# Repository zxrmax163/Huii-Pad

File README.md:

# Huii-Pad 

Is a small Macropad wich has 10 keys and a oled screen.

the cas is desinged to be printed in FDM with a pressfit cover and a SLA printed window for the controller. The case holds together by friction and the pcb gets screwt in with M3 Bolts and is hold by M3 Nuts in the case.

# PCB

The PCB is 100mm width and has a lenght of 68mm.

# Firmware

KMK with support for OLED screen.

# BOM

10x Cherry MX Switches

10x DSA Keycaps

1x 0.91" 128x32 OLED Display

1x XIAO RP2040

1x Case (3d printed parts)

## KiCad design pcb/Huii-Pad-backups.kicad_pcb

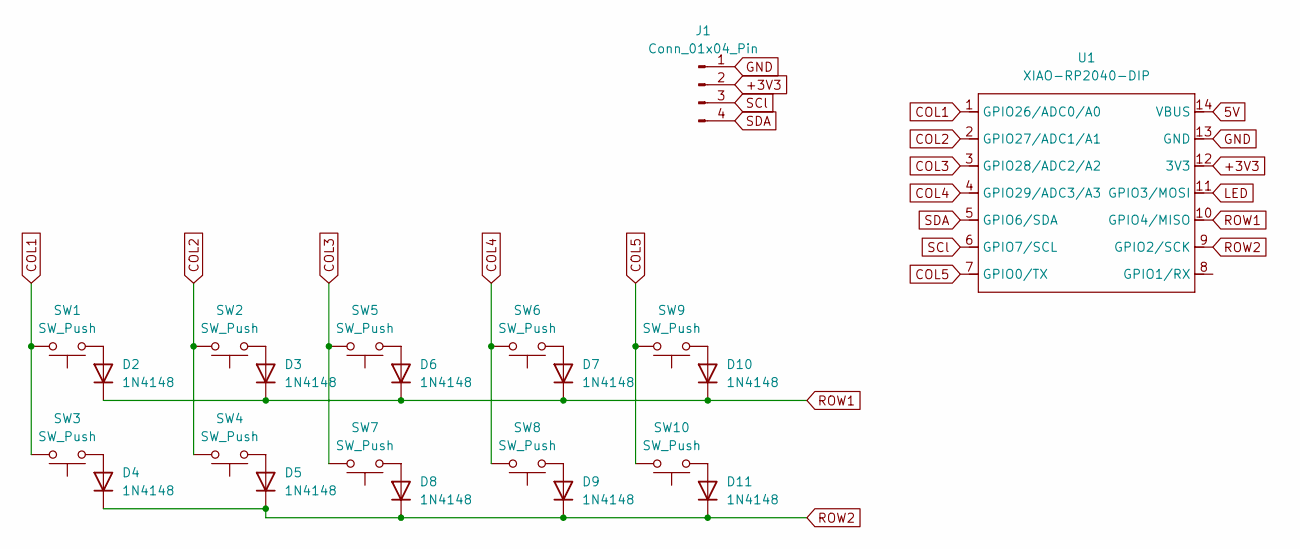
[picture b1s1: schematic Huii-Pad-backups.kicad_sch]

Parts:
D2, D3, D4, D5, D6, D7, D8, D9, D10, D11: 1N4148; D_DO-35_SOD27_P7.62mm_Horizontal
J1: Conn_01x04_Pin; SSD1306-0.91-OLED-4pin-128x32
SW1, SW2, SW3, SW4, SW5, SW6, SW7, SW8, SW9, SW10: SW_Push; SW_Cherry_MX_1.00u_PCB
U1: XIAO-RP2040-DIP

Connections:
5V: U1.14 (VBUS)
+3V3: J1.2, U1.12 (3V3)
COL1: SW1.2, SW3.2, U1.1 (GPIO26/ADC0/A0)
COL2: SW2.2, SW4.2, U1.2 (GPIO27/ADC1/A1)
COL3: SW5.2, SW7.2, U1.3 (GPIO28/ADC2/A2)
COL4: SW6.2, SW8.2, U1.4 (GPIO29/ADC3/A3)
COL5: SW9.2, SW10.2, U1.7 (GPIO0/TX)
GND: J1.1, U1.13 (GND)
LED: U1.11 (GPIO3/MOSI)
unnamed: D2.2 (A), SW1.1
unnamed: D3.2 (A), SW2.1
unnamed: D4.2 (A), SW3.1
unnamed: D5.2 (A), SW4.1
unnamed: D6.2 (A), SW5.1
unnamed: D7.2 (A), SW6.1
unnamed: D8.2 (A), SW7.1
unnamed: D9.2 (A), SW8.1
unnamed: D10.2 (A), SW9.1
unnamed: D11.2 (A), SW10.1
ROW1: D2.1 (K), D3.1 (K), D6.1 (K), D7.1 (K), D10.1 (K), U1.10 (GPIO4/MISO)
ROW2: D4.1 (K), D5.1 (K), D8.1 (K), D9.1 (K), D11.1 (K), U1.9 (GPIO2/SCK)
SCl: J1.3, U1.6 (GPIO7/SCL)
SDA: J1.4, U1.5 (GPIO6/SDA)

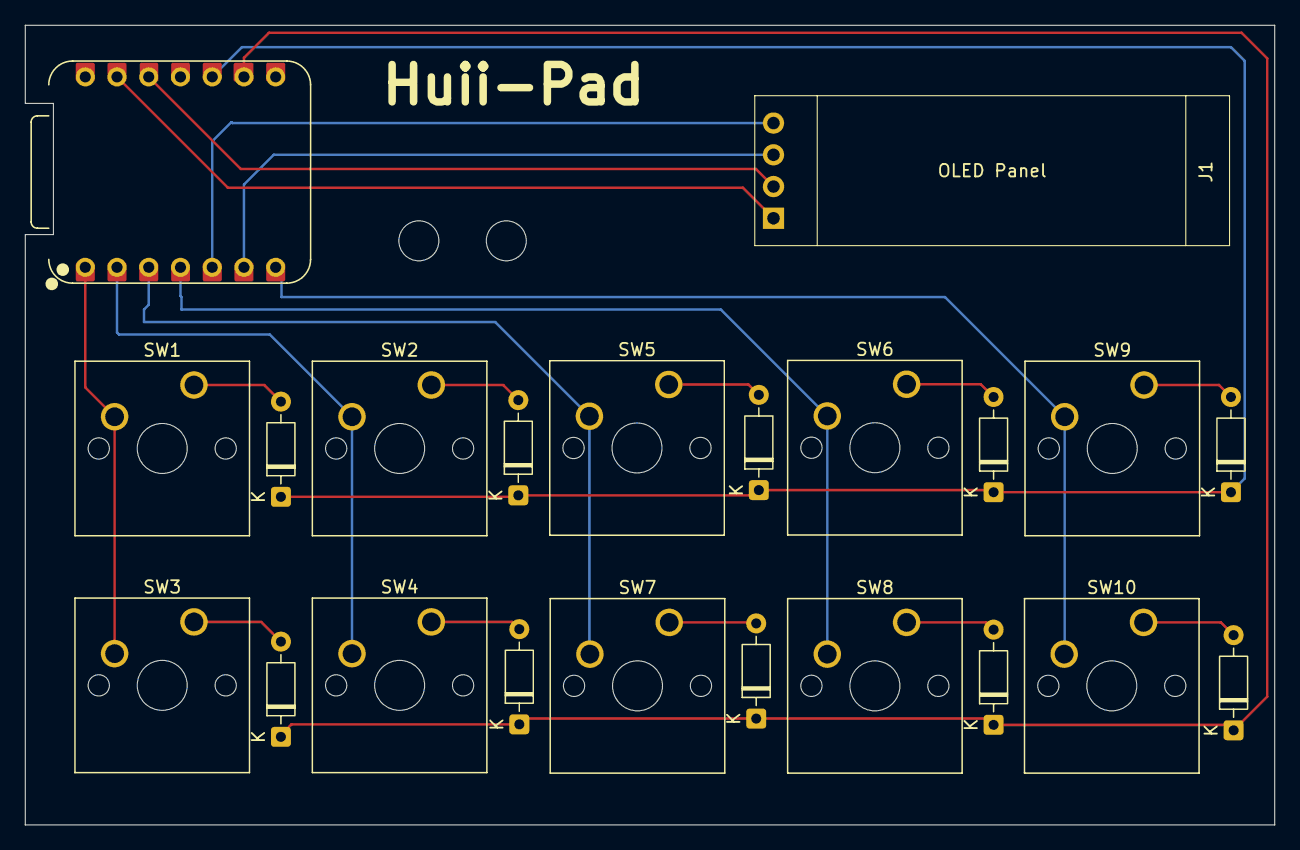
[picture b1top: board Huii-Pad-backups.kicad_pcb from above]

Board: 2 copper layers, 100.0 x 64.0 mm, 22 parts (0 on the bottom side), 21 nets.

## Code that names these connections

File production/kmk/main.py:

import board
import busio

#kmk stuff
from kmk.kmk_keyboard import KMKKeyboard
from kmk.scanners.keypad import KeysScanner
from kmk.keys import KC
from kmk.modules.macros import Press, Release, Tap, Macros
from kmk.modules.encoder import EncoderHandler
from kmk.extensions.display import Display, TextEntry
from kmk.extensions.display.ssd1306 import SSD1306
from kmk.scanners.keypad import MatrixScanner

# initializing the keyboard
keyboard = KMKKeyboard()

# macro setup
macros = Macros()
keyboard.modules.append(macros)


# pin setup
PINS = [board.GPIO26, board.GPIO27, board.GPIO28, board.GPIO29, board.GPIO4, board.GPIO5, board.GPIO0]


# display setup
bus = busio.I2C(board.GP_SCL, board.GP_SDA)
driver = SSD1306(i2c=bus, device_address=0x3C)

display = Display(
    display=driver,
    width=128,
    height=32,
    flip = False,
    dim_time=10,
    dim_target=0.2,
    off_time=1200,
    brightness=0.8
)

# display action
display.entries = [
        TextEntry(text="Huii", x=64, y=16, x_anchor="M", y_anchor="M"),
]

keyboard.matrix = MatrixScanner(
    rows=(board.GPIO4, board.GPIO5,),
    cols=(board.GPIO26, board.GPIO27, board.GPIO28, board.GPIO29, board.GPIO0),
    value_when_pressed=False,
)

keyboard.keymap = [
    [KC.1, KC.2, KC.3,KC.4, KC.5,
     KC.6, KC.7, KC.8, KC.9, KC.0]
]
   

# starting kmk
if __name__ == '__main__':
    keyboard.go()

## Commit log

2025-07-09 Readme
2025-07-14 pictures
